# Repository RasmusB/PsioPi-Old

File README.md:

# PsioPi
Hardware upgrade project for the Psion Series 5/5mx

There is a project log maintained at http://hackaday.io/project/4042 

This repository contains the latest development on the PsioPi project.

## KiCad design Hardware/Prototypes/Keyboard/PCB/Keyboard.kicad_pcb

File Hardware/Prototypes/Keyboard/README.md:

# Keyboard prototype

An ATmega32u4 based keyboard controller.

* PCB contains KiCad files for a prototype USB board
* Psion-Keyboard-Firmware contains an Arduino sketch for the firmware
* ScanTheMatrix is a sketch for scanning the matrix of an unknown keyboard

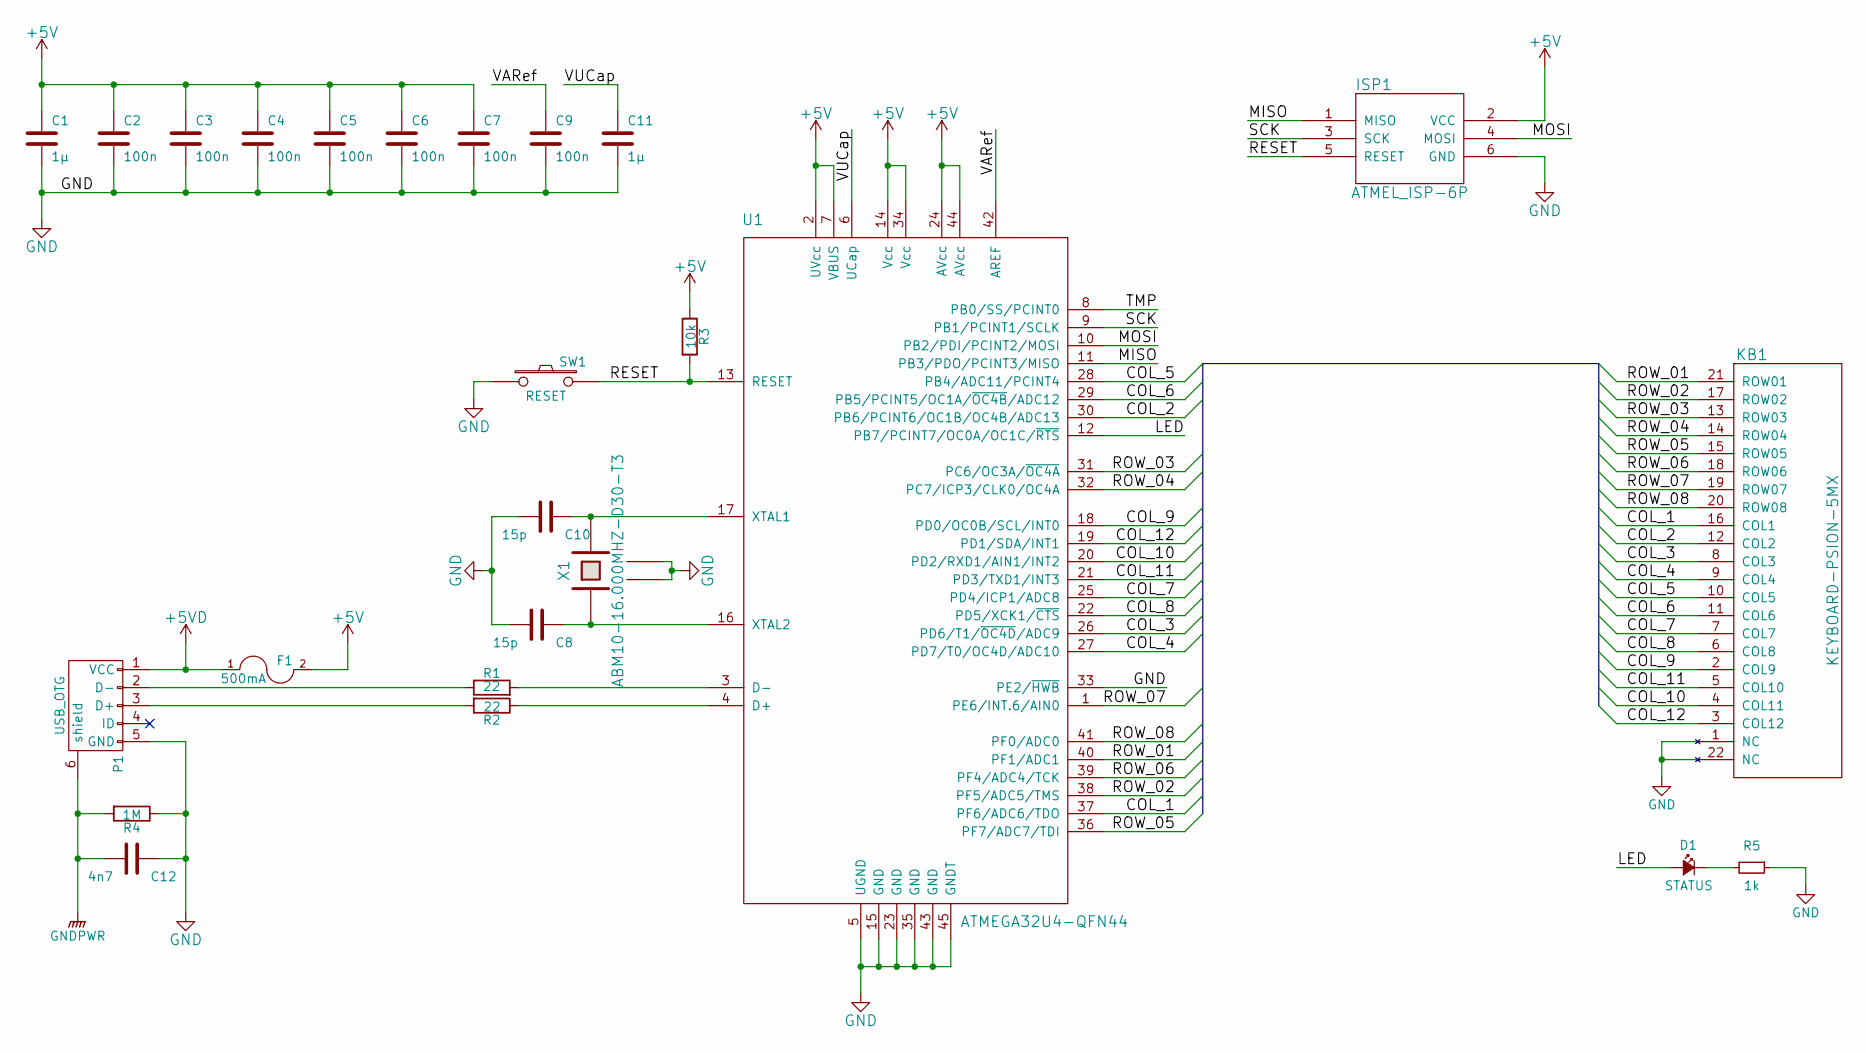
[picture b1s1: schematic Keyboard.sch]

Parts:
C1, C11: 1µ; C-0402-1005
C2, C3, C4, C5, C6, C7, C9: 100n; C-0402-1005
C8, C10: 15p; C-0402-1005
C12: 4n7; C-0402-1005
D1: STATUS; LED-0402-1005
F1: 500mA; F-0603-1608; Farnell 1717227
ISP1: ATMEL_ISP-6P; ISP-PADS_2mm54
KB1: KEYBOARD-PSION-5MX; FPC_0.5mm_22p-MOLEX_52437; Farnell 2520146
P1: USB_OTG; USB-MICRO-MOLEX-47491-0001; Farnell 1568025
R1, R2: 22; R-0402-1005
R3: 10k; R-0402-1005
R4: 1M; R-0402-1005
R5: 1k; R-0402-1005
SW1: RESET; KSR251GLFS; Farnell 2376538
U1: ATMEGA32U4-QFN44; VQFN-44_ATMEL; Farnell 2425127
X1: ABM10-16.000MHZ-D30-T3; 2.5x2mm; Farnell 2467762

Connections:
+5V: C1.1, C2.1, C3.1, C4.1, C5.1, C6.1, C7.1, F1.2, ISP1.2 (VCC), R3.1, U1.2 (UVcc), U1.7 (VBUS), U1.14 (Vcc), U1.24 (AVcc), U1.34 (Vcc), U1.44 (AVcc)
+5VD: F1.1, P1.1 (VCC)
/COL_1: KB1.16 (COL1), U1.37 (PF6/ADC6/TDO)
/COL_2: KB1.12 (COL2), U1.30 (PB6/PCINT6/OC1B/OC4B/ADC13)
/COL_3: KB1.8 (COL3), U1.26 (PD6/T1/~OC4D~/ADC9)
/COL_4: KB1.9 (COL4), U1.27 (PD7/T0/OC4D/ADC10)
/COL_5: KB1.10 (COL5), U1.28 (PB4/ADC11/PCINT4)
/COL_6: KB1.11 (COL6), U1.29 (PB5/PCINT5/OC1A/~OC4B~/ADC12)
/COL_7: KB1.7 (COL7), U1.25 (PD4/ICP1/ADC8)
/COL_8: KB1.6 (COL8), U1.22 (PD5/XCK1/~CTS)
/COL_9: KB1.2 (COL9), U1.18 (PD0/OC0B/SCL/INT0)
/COL_10: KB1.4 (COL11), U1.20 (PD2/RXD1/AIN1/INT2)
/COL_11: KB1.5 (COL10), U1.21 (PD3/TXD1/INT3)
/COL_12: KB1.3 (COL12), U1.19 (PD1/SDA/INT1)
/LED: D1.2 (A), U1.12 (PB7/PCINT7/OC0A/OC1C/~RTS)
/MISO: ISP1.1 (MISO), U1.11 (PB3/PDO/PCINT3/MISO)
/MOSI: ISP1.4 (MOSI), U1.10 (PB2/PDI/PCINT2/MOSI)
/RESET: ISP1.5 (RESET), R3.2, SW1.2, U1.13 (RESET)
/ROW_01: KB1.21 (ROW01), U1.40 (PF1/ADC1)
/ROW_02: KB1.17 (ROW02), U1.38 (PF5/ADC5/TMS)
/ROW_03: KB1.13 (ROW03), U1.31 (PC6/OC3A/~OC4A)
/ROW_04: KB1.14 (ROW04), U1.32 (PC7/ICP3/CLK0/OC4A)
/ROW_05: KB1.15 (ROW05), U1.36 (PF7/ADC7/TDI)
/ROW_06: KB1.18 (ROW06), U1.39 (PF4/ADC4/TCK)
/ROW_07: KB1.19 (ROW07), U1.1 (PE6/INT.6/AIN0)
/ROW_08: KB1.20 (ROW08), U1.41 (PF0/ADC0)
/SCK: ISP1.3 (SCK), U1.9 (PB1/PCINT1/SCLK)
/VARef: C9.1, U1.42 (AREF)
/VUCap: C11.1, U1.6 (UCap)
GND: C1.2, C2.2, C3.2, C4.2, C5.2, C6.2, C7.2, C8.2, C9.2, C10.2, C11.2, C12.1, ISP1.6 (GND), KB1.1 (NC), KB1.22 (NC), P1.5 (GND), R4.1, R5.1, SW1.1, U1.5 (UGND), U1.15 (GND), U1.23 (GND), U1.33 (PE2/~HWB), U1.35 (GND), U1.43 (GND), U1.45 (GNDT), X1.2 (GND), X1.4 (GND)
GNDPWR: C12.2, P1.6 (shield), R4.2
unnamed: C8.1, U1.16 (XTAL2), X1.1
unnamed: C10.1, U1.17 (XTAL1), X1.3
unnamed: D1.1 (K), R5.2
unnamed: P1.2 (D-), R1.1
unnamed: P1.3 (D+), R2.2
unnamed: R1.2, U1.3 (D-)
unnamed: R2.1, U1.4 (D+)

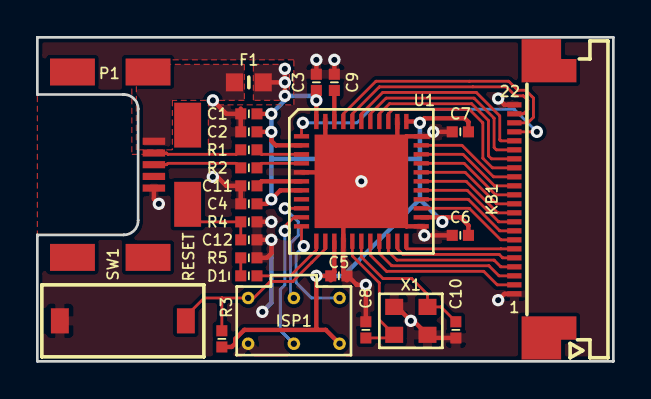
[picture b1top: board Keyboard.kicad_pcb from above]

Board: 2 copper layers, 32.0 x 18.0 mm, 25 parts (0 on the bottom side), 38 nets.

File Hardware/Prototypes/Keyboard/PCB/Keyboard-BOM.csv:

Reference, Value, Footprint, Datasheet, Farnell
KB1,KEYBOARD-PSION-5MX,SMD-Connectors:FPC_0.5mm_22p-MOLEX_52437,,2520146
U1,ATMEGA32U4-QFN44,SMD-QFN:VQFN-44_ATMEL,,2425127
C4,100n,SMD-DiscreteB:C-0402-1005,
C5,100n,SMD-DiscreteB:C-0402-1005,
C6,100n,SMD-DiscreteB:C-0402-1005,
C7,100n,SMD-DiscreteB:C-0402-1005,
C1,1µ,SMD-DiscreteB:C-0402-1005,
C3,100n,SMD-DiscreteB:C-0402-1005,
C9,100n,SMD-DiscreteB:C-0402-1005,
C11,1µ,SMD-DiscreteB:C-0402-1005,
X1,ABM10-16.000MHZ-D30-T3,SMD-XTAL:2.5x2mm,,2467762
C10,15p,SMD-DiscreteB:C-0402-1005,
C8,15p,SMD-DiscreteB:C-0402-1005,
C2,100n,SMD-DiscreteB:C-0402-1005,
R1,22,SMD-DiscreteB:R-0402-1005,
R2,22,SMD-DiscreteB:R-0402-1005,
F1,500mA,SMD-DiscreteB:0603-1608,,1717227
R3,10k,SMD-DiscreteB:R-0402-1005,
ISP1,ATMEL_ISP-6P,SMD-Connectors:ISP-PADS_2mm54,
P1,USB_OTG,SMD-Connectors:USB-MICRO-MOLEX-47491-0001,,1568025
R4,1M,SMD-DiscreteB:R-0402-1005,
C12,4n7,SMD-DiscreteB:C-0402-1005,
D1,STATUS,SMD-DiscreteB:LED-0402-1005,
R5,1k,SMD-DiscreteB:R-0402-1005,
SW1,RESET,SMD-Switches:KSR251GLFS,,2376538

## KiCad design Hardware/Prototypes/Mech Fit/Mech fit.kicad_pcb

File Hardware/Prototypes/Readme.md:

# Prototypes

This folder contains prototypes of different sub-modules. None of these are needed for building a PsioPi, but if you want to use just part of the project, these modules might be a good place to start.

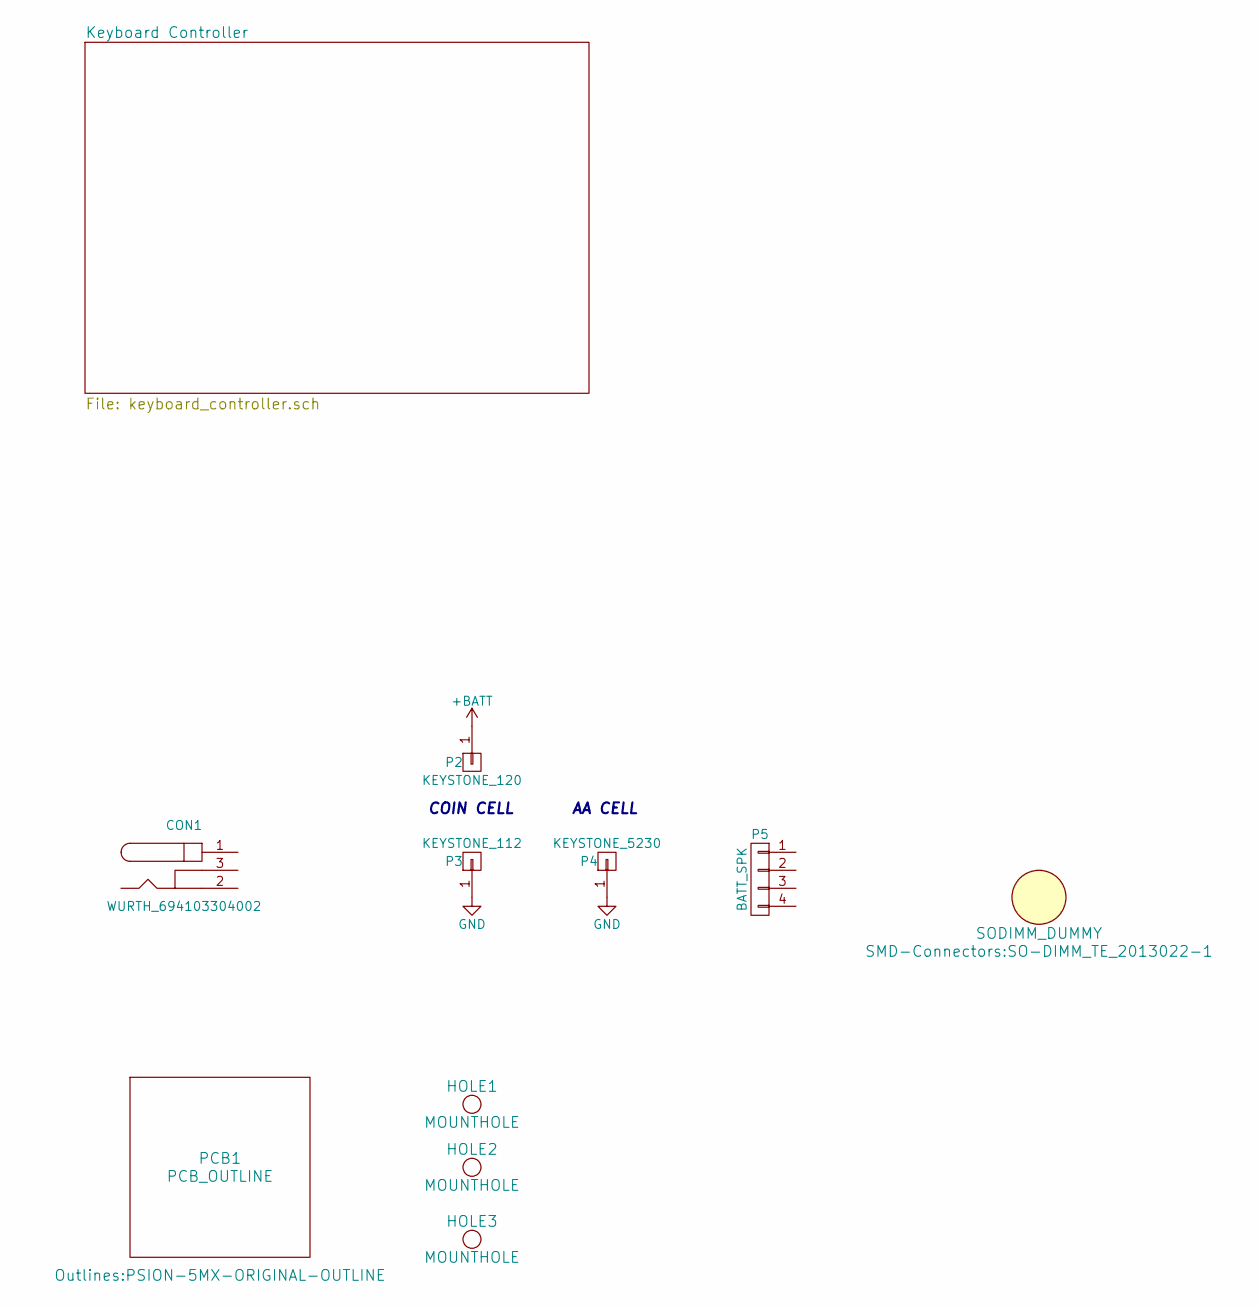
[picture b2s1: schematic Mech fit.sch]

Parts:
CON1: WURTH_694103304002; DC-JACK_WURTH-694103304002; Farnell 2472145
HOLE1, HOLE2, HOLE3: MOUNTHOLE; HOLE-2mm2-NPTH
K1: SODIMM_DUMMY; SO-DIMM_TE_2013022-1
P2: KEYSTONE_120; COIN_CELL_POSITIVE-KEYSTONE_120
P3: KEYSTONE_112; COIN_CELL_NEGATIVE-KEYSTONE_112
P4: KEYSTONE_5230; AAA_CELL_CONTACT-KEYSTONE_5230-DUAL
P5: BATT_SPK; FPC_1mm_4p-TE-84953-4; Farnell 1245278
PCB1: PCB_OUTLINE; PSION-5MX-ORIGINAL-OUTLINE

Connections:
GND: P3.1, P4.1; also elsewhere on the board

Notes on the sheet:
COIN CELL
AA CELL

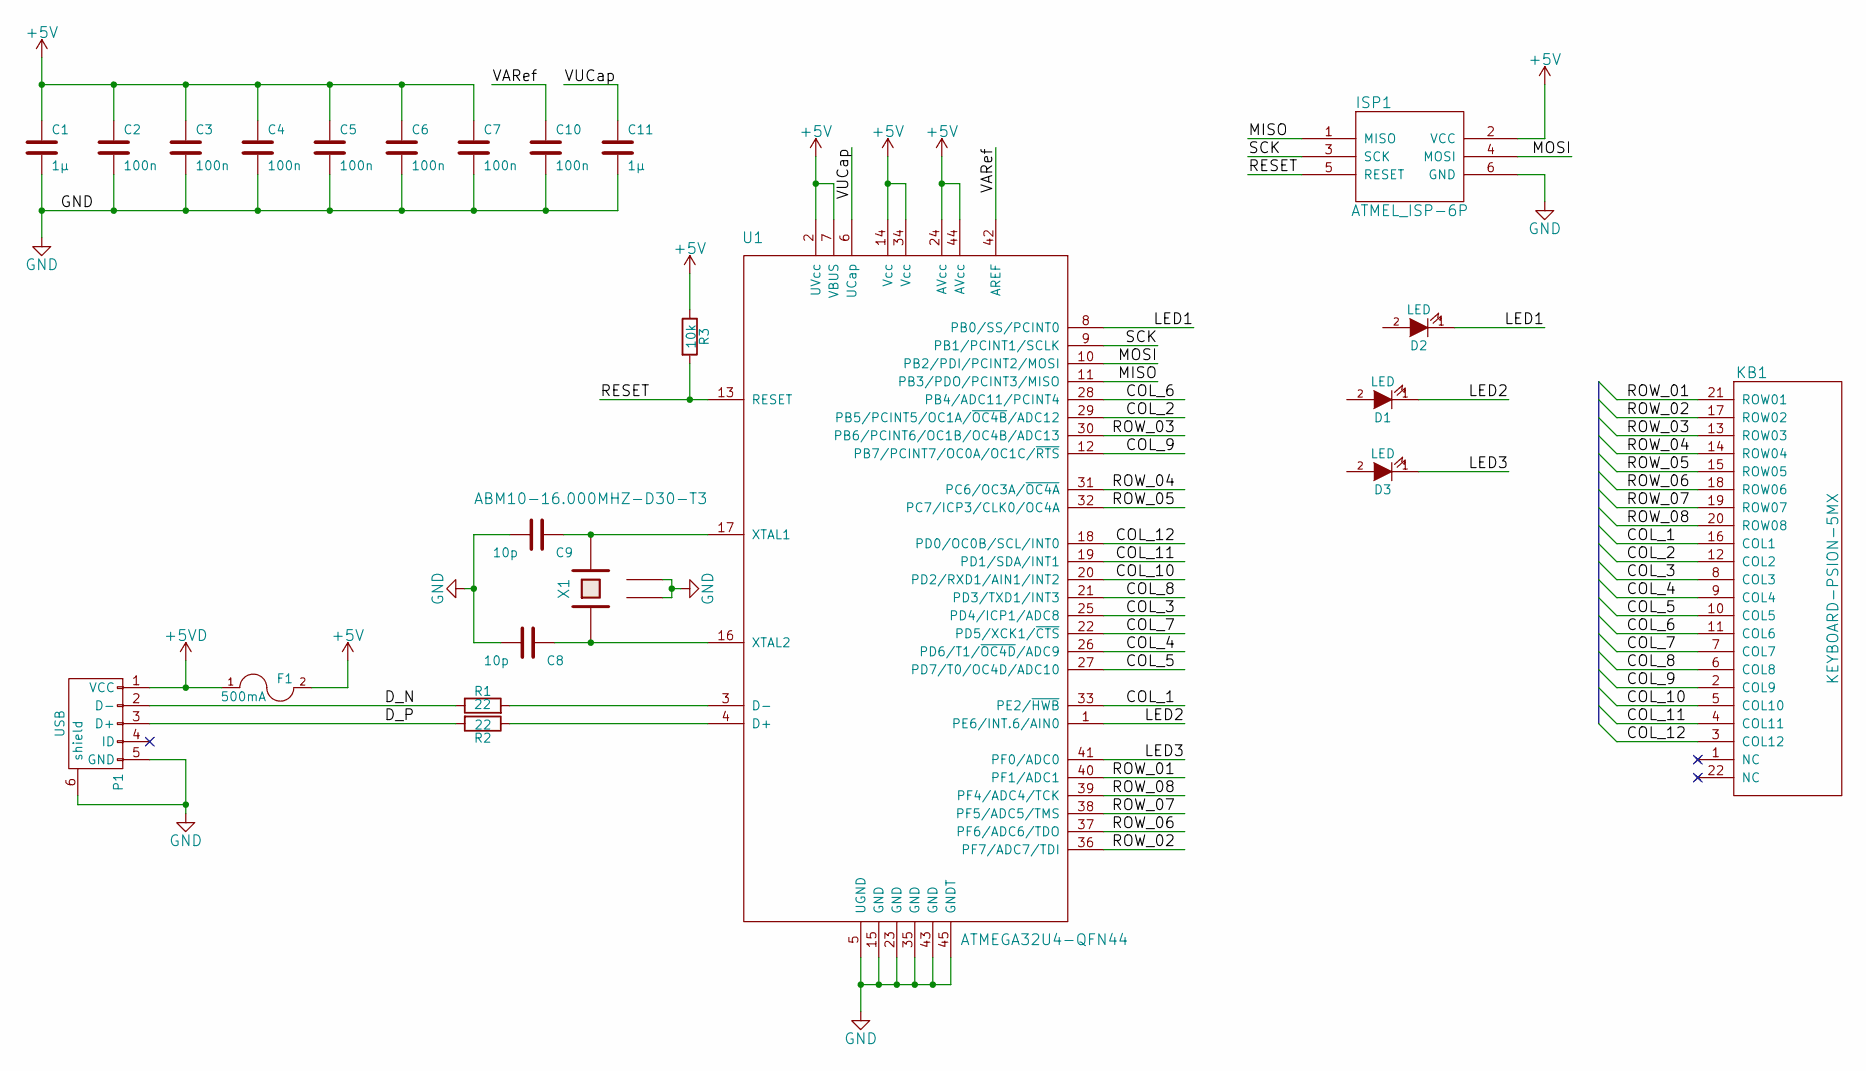
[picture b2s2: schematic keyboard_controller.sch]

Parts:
C1, C11: 1µ; C-0402-1005
C2, C3, C4, C5, C6, C7, C10: 100n; C-0402-1005
C8, C9: 10p; C-0402-1005
D1, D2, D3: LED; LED-0402-1005
F1: 500mA; 0603-1608
ISP1: ATMEL_ISP-6P; ISP-PADS_1x6_2mm54
KB1: KEYBOARD-PSION-5MX; FPC_0mm5_22p-WURTH-68712214522; Farnell 2520146
P1: USB; USB-MICRO-MOLEX-47491-0001; Farnell 1568025
R1, R2: 22; R-0402-1005
R3: 10k; R-0402-1005
U1: ATMEGA32U4-QFN44; VQFN-44_ATMEL
X1: ABM10-16.000MHZ-D30-T3; 2.5x2mm

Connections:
+5V: C1.1, C2.1, C3.1, C4.1, C5.1, C6.1, C7.1, F1.2, ISP1.2 (VCC), R3.1, U1.2 (UVcc), U1.7 (VBUS), U1.14 (Vcc), U1.24 (AVcc), U1.34 (Vcc), U1.44 (AVcc)
+5VD: F1.1, P1.1 (VCC)
/Keyboard Controller/COL_1: KB1.16 (COL1), U1.33 (PE2/~HWB)
/Keyboard Controller/COL_2: KB1.12 (COL2), U1.29 (PB5/PCINT5/OC1A/~OC4B~/ADC12)
/Keyboard Controller/COL_3: KB1.8 (COL3), U1.25 (PD4/ICP1/ADC8)
/Keyboard Controller/COL_4: KB1.9 (COL4), U1.26 (PD6/T1/~OC4D~/ADC9)
/Keyboard Controller/COL_5: KB1.10 (COL5), U1.27 (PD7/T0/OC4D/ADC10)
/Keyboard Controller/COL_6: KB1.11 (COL6), U1.28 (PB4/ADC11/PCINT4)
/Keyboard Controller/COL_7: KB1.7 (COL7), U1.22 (PD5/XCK1/~CTS)
/Keyboard Controller/COL_8: KB1.6 (COL8), U1.21 (PD3/TXD1/INT3)
/Keyboard Controller/COL_9: KB1.2 (COL9), U1.12 (PB7/PCINT7/OC0A/OC1C/~RTS)
/Keyboard Controller/COL_10: KB1.5 (COL10), U1.20 (PD2/RXD1/AIN1/INT2)
/Keyboard Controller/COL_11: KB1.4 (COL11), U1.19 (PD1/SDA/INT1)
/Keyboard Controller/COL_12: KB1.3 (COL12), U1.18 (PD0/OC0B/SCL/INT0)
/Keyboard Controller/D_N: P1.2 (D-), R1.1
/Keyboard Controller/D_P: P1.3 (D+), R2.2
/Keyboard Controller/LED1: D2.1 (K), U1.8 (PB0/SS/PCINT0)
/Keyboard Controller/LED2: D1.1 (K), U1.1 (PE6/INT.6/AIN0)
/Keyboard Controller/LED3: D3.1 (K), U1.41 (PF0/ADC0)
/Keyboard Controller/MISO: ISP1.1 (MISO), U1.11 (PB3/PDO/PCINT3/MISO)
/Keyboard Controller/MOSI: ISP1.4 (MOSI), U1.10 (PB2/PDI/PCINT2/MOSI)
/Keyboard Controller/RESET: ISP1.5 (RESET), R3.2, U1.13 (RESET)
/Keyboard Controller/ROW_01: KB1.21 (ROW01), U1.40 (PF1/ADC1)
/Keyboard Controller/ROW_02: KB1.17 (ROW02), U1.36 (PF7/ADC7/TDI)
/Keyboard Controller/ROW_03: KB1.13 (ROW03), U1.30 (PB6/PCINT6/OC1B/OC4B/ADC13)
/Keyboard Controller/ROW_04: KB1.14 (ROW04), U1.31 (PC6/OC3A/~OC4A)
/Keyboard Controller/ROW_05: KB1.15 (ROW05), U1.32 (PC7/ICP3/CLK0/OC4A)
/Keyboard Controller/ROW_06: KB1.18 (ROW06), U1.37 (PF6/ADC6/TDO)
/Keyboard Controller/ROW_07: KB1.19 (ROW07), U1.38 (PF5/ADC5/TMS)
/Keyboard Controller/ROW_08: KB1.20 (ROW08), U1.39 (PF4/ADC4/TCK)
/Keyboard Controller/SCK: ISP1.3 (SCK), U1.9 (PB1/PCINT1/SCLK)
/Keyboard Controller/VARef: C10.1, U1.42 (AREF)
/Keyboard Controller/VUCap: C11.1, U1.6 (UCap)
GND: C1.2, C2.2, C3.2, C4.2, C5.2, C6.2, C7.2, C8.2, C9.2, C10.2, C11.2, ISP1.6 (GND), P1.5 (GND), P1.6 (shield), U1.5 (UGND), U1.15 (GND), U1.23 (GND), U1.35 (GND), U1.43 (GND), U1.45 (GNDT), X1.2 (GND), X1.4 (GND); also elsewhere on the board
unnamed: C8.1, U1.16 (XTAL2), X1.1
unnamed: C9.1, U1.17 (XTAL1), X1.3
unnamed: R1.2, U1.3 (D-)
unnamed: R2.1, U1.4 (D+)

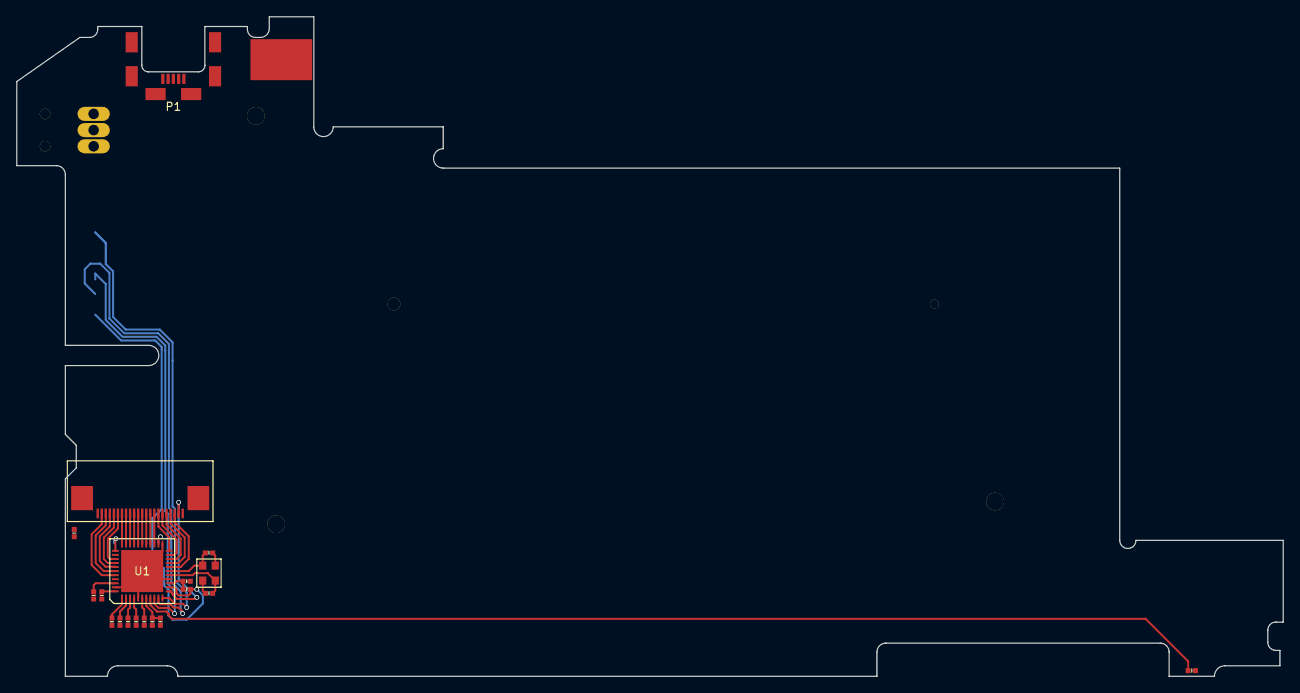
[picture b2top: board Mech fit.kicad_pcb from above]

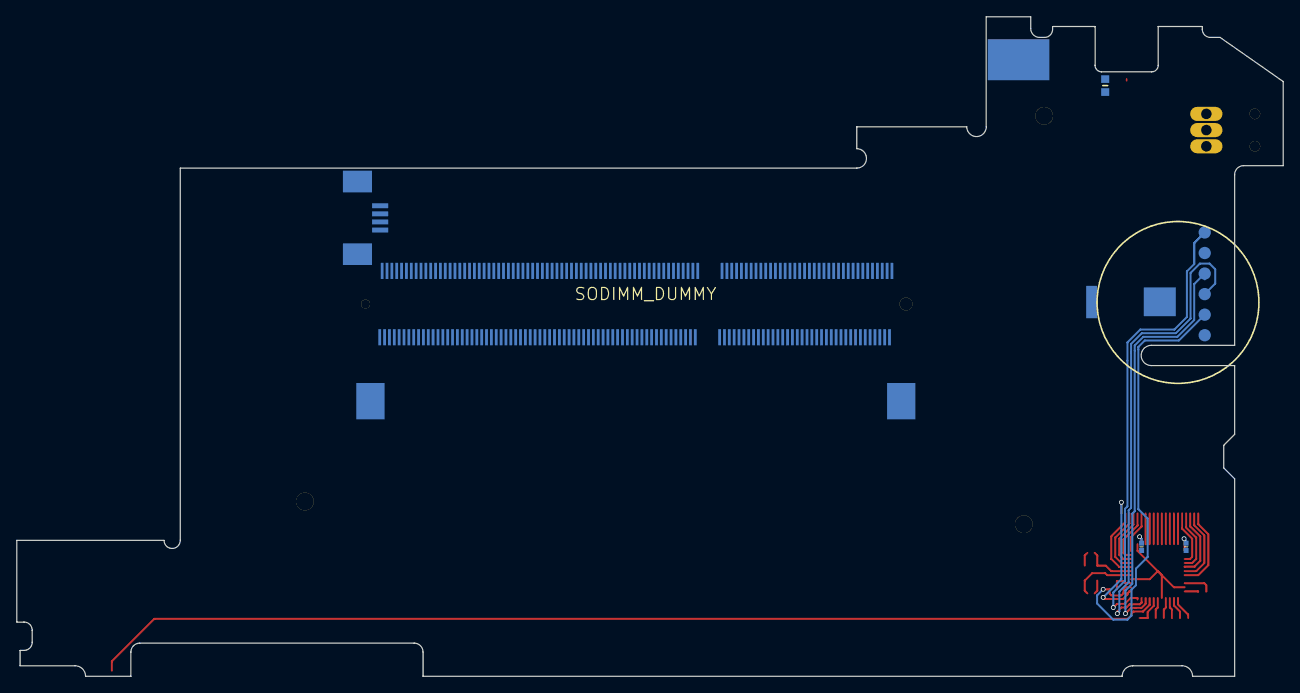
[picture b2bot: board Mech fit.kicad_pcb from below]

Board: 2 copper layers, 156.5 x 81.5 mm, 33 parts (9 on the bottom side), 38 nets.

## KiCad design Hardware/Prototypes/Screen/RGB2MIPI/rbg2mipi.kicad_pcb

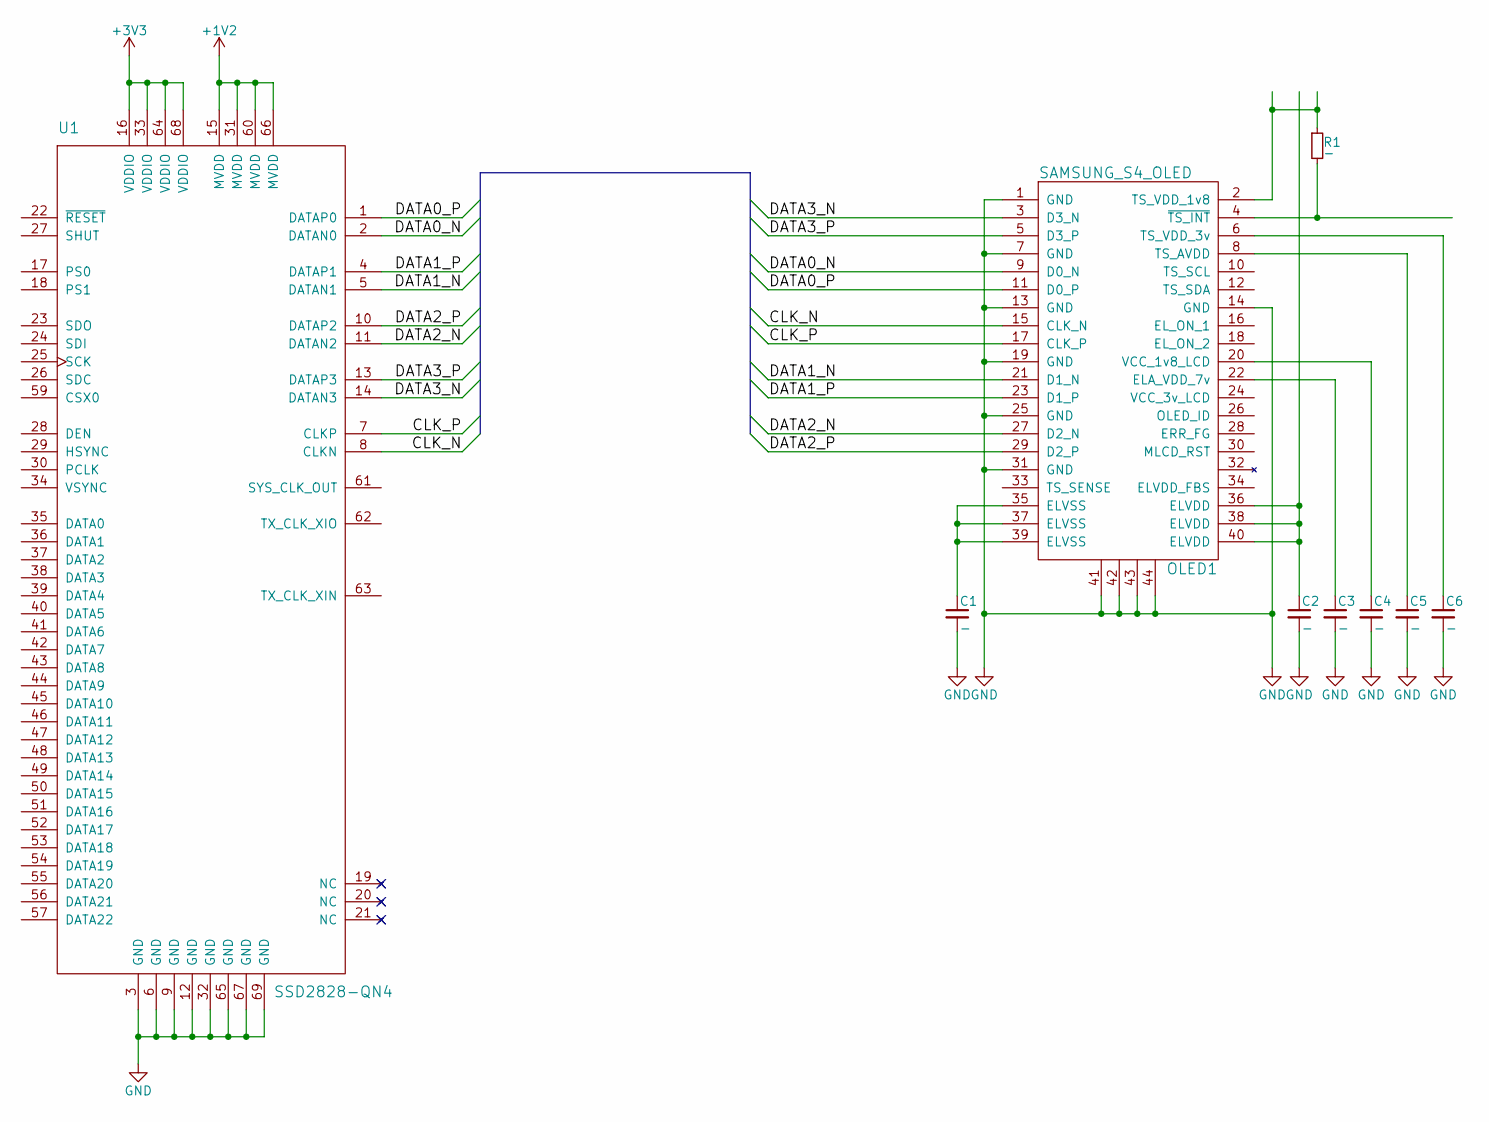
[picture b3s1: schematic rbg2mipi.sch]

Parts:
C1, C2, C3, C4, C5, C6: -; C-0402-1005
OLED1: SAMSUNG_S4_OLED; PANASONIC-AXE640124-SAMSUNG-S4
R1: -; R-0402-1005
U1: SSD2828-QN4; QFN64_8x8mm_0mm4-SSD

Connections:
+1V2: U1.15 (MVDD), U1.31 (MVDD), U1.60 (MVDD), U1.66 (MVDD)
+3V3: U1.16 (VDDIO), U1.33 (VDDIO), U1.64 (VDDIO), U1.68 (VDDIO)
/CLK_N: OLED1.15 (CLK_N), U1.8 (CLKN)
/CLK_P: OLED1.17 (CLK_P), U1.7 (CLKP)
/DATA0_N: OLED1.9 (D0_N), U1.2 (DATAN0)
/DATA0_P: OLED1.11 (D0_P), U1.1 (DATAP0)
/DATA1_N: OLED1.21 (D1_N), U1.5 (DATAN1)
/DATA1_P: OLED1.23 (D1_P), U1.4 (DATAP1)
/DATA2_N: OLED1.27 (D2_N), U1.11 (DATAN2)
/DATA2_P: OLED1.29 (D2_P), U1.10 (DATAP2)
/DATA3_N: OLED1.3 (D3_N), U1.14 (DATAN3)
/DATA3_P: OLED1.5 (D3_P), U1.13 (DATAP3)
GND: C1.2, C2.2, C3.2, C4.2, C5.2, C6.2, OLED1.1 (GND), OLED1.7 (GND), OLED1.13 (GND), OLED1.14 (GND), OLED1.19 (GND), OLED1.25 (GND), OLED1.31 (GND), OLED1.41, OLED1.42, OLED1.43, OLED1.44, U1.3 (GND), U1.6 (GND), U1.9 (GND), U1.12 (GND), U1.32 (GND), U1.65 (GND), U1.67 (GND), U1.69 (GND)
unnamed: C1.1, OLED1.35 (ELVSS), OLED1.37 (ELVSS), OLED1.39 (ELVSS)
unnamed: C2.1, OLED1.36 (ELVDD), OLED1.38 (ELVDD), OLED1.40 (ELVDD)
unnamed: C3.1, OLED1.22 (ELA_VDD_7v)
unnamed: C4.1, OLED1.20 (VCC_1v8_LCD)
unnamed: C5.1, OLED1.8 (TS_AVDD)
unnamed: C6.1, OLED1.6 (TS_VDD_3v)
unnamed: OLED1.2 (TS_VDD_1v8), R1.1
unnamed: OLED1.4 (~TS_INT), R1.2

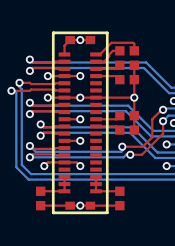
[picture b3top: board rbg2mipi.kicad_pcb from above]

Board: 2 copper layers, 9 parts (1 on the bottom side), 21 nets.

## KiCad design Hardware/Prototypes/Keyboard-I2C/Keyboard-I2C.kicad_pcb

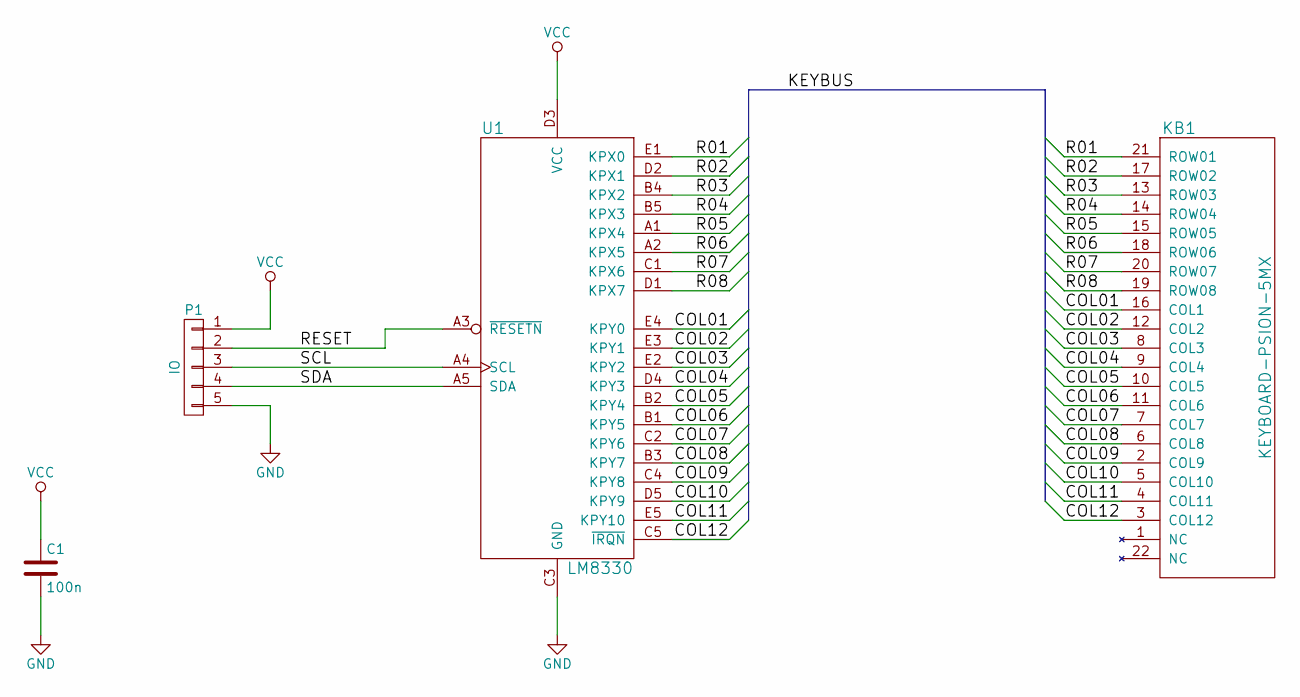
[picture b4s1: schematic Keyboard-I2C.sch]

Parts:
C1: 100n; C-0402-1005
KB1: KEYBOARD-PSION-5MX; FPC_0.5mm_22p-MOLEX_52437
P1: IO; PIN_HEADER-1x5
U1: LM8330; DSBGA-25_2x2_0mm4

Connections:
/COL01: KB1.16 (COL1), U1.E4 (KPY0)
/COL02: KB1.12 (COL2), U1.E3 (KPY1)
/COL03: KB1.8 (COL3), U1.E2 (KPY2)
/COL04: KB1.9 (COL4), U1.D4 (KPY3)
/COL05: KB1.10 (COL5), U1.B2 (KPY4)
/COL06: KB1.11 (COL6), U1.B1 (KPY5)
/COL07: KB1.7 (COL7), U1.C2 (KPY6)
/COL08: KB1.6 (COL8), U1.B3 (KPY7)
/COL09: KB1.2 (COL9), U1.C4 (KPY8)
/COL10: KB1.5 (COL10), U1.D5 (KPY9)
/COL11: KB1.4 (COL11), U1.E5 (KPY10)
/COL12: KB1.3 (COL12), U1.C5 (~IRQN)
/R01: KB1.21 (ROW01), U1.E1 (KPX0)
/R02: KB1.17 (ROW02), U1.D2 (KPX1)
/R03: KB1.13 (ROW03), U1.B4 (KPX2)
/R04: KB1.14 (ROW04), U1.B5 (KPX3)
/R05: KB1.15 (ROW05), U1.A1 (KPX4)
/R06: KB1.18 (ROW06), U1.A2 (KPX5)
/R07: KB1.20 (ROW07), U1.C1 (KPX6)
/R08: KB1.19 (ROW08), U1.D1 (KPX7)
/RESET: P1.2, U1.A3 (~RESETN)
/SCL: P1.3, U1.A4 (SCL)
/SDA: P1.4, U1.A5 (SDA)
GND: C1.2, P1.5, U1.C3 (GND)
VCC: C1.1, P1.1, U1.D3 (VCC)

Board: 2 copper layers, 4 parts (0 on the bottom side), 25 nets, no tracks yet.

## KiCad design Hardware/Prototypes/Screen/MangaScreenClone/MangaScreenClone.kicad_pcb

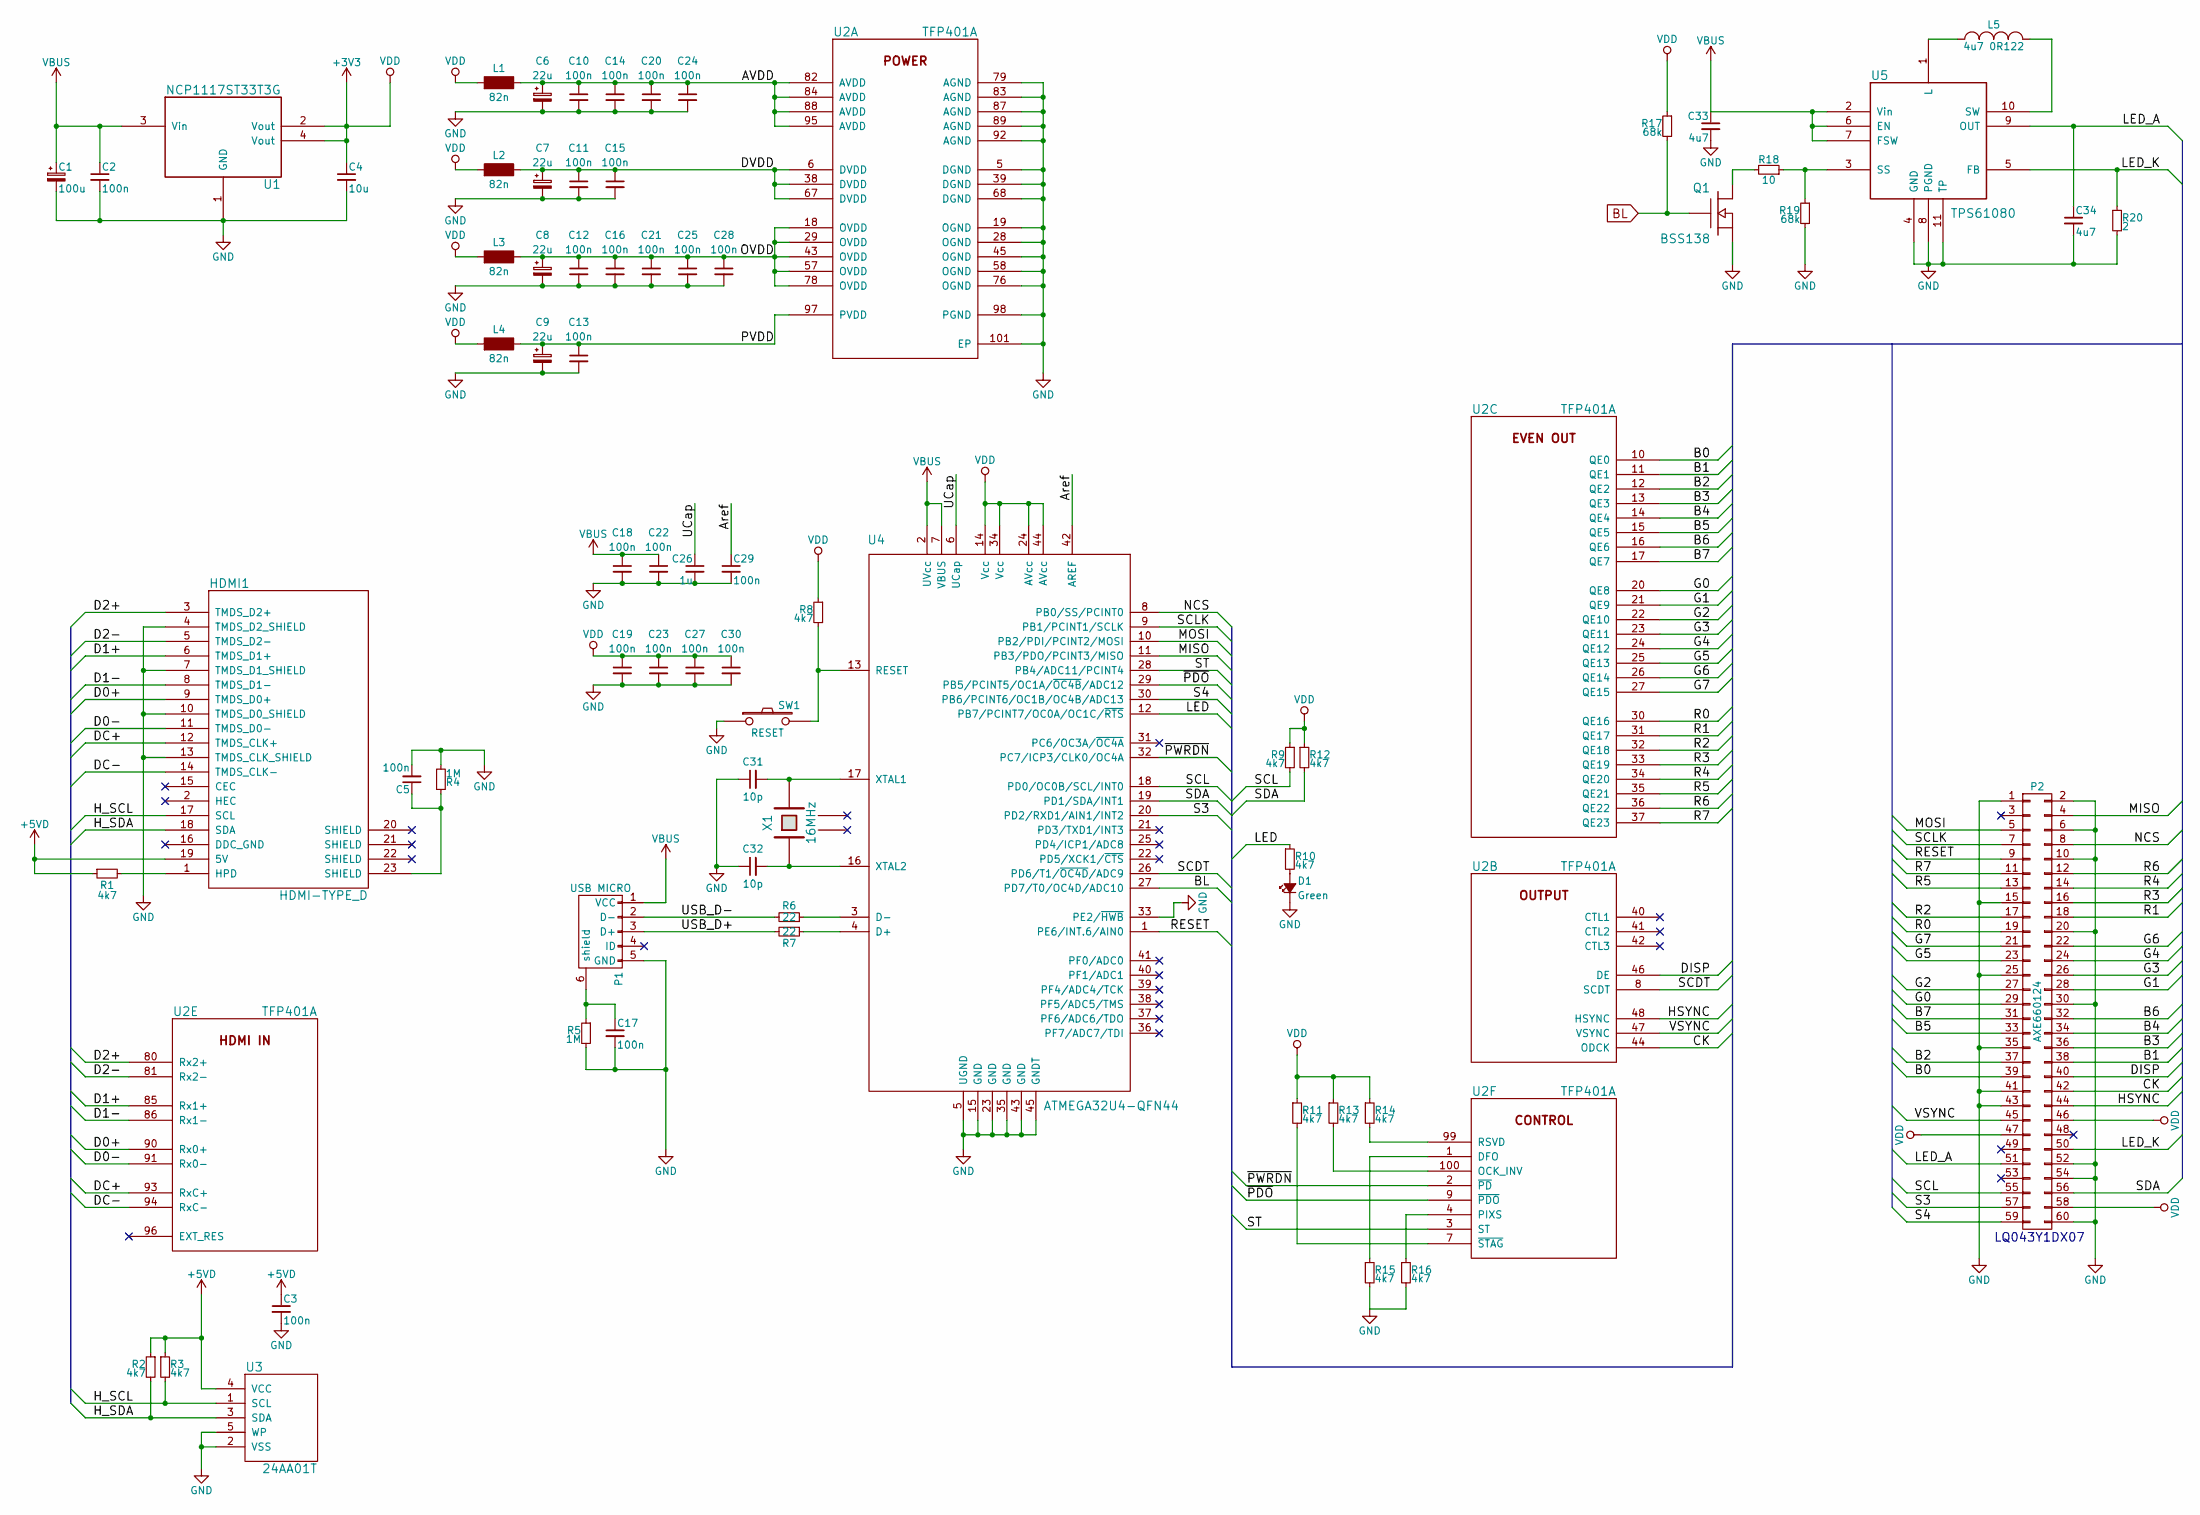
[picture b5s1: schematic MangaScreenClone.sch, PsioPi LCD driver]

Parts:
C1: 100u; B-3528-21; Farnell 1658510
C2, C3, C5, C10, C11, C12, C13, C14, C15, C16, C17, C18, C19, C20, C21, C22, C23, C24, C25, C27, C28, C29, C30: 100n; C-0402-1005
C4: 10u; C-0402-1005; Farnell 2218854
C6, C7, C8, C9: 22u; A-3216-18; Farnell 1457420
C26: 1u; C-0402-1005
C31, C32: 10p; C-0402-1005
C33, C34: 4u7; C-0402-1005
D1: Green; LED-0402-1005
HDMI1: HDMI-TYPE_D; HDMI-D_MOLEX_46765-0301
L1, L2, L3, L4: 82n; 0805-2012; Farnell 1669556
L5: 4u7 0R122; L_5x5mm_TDK-VLCF5020--1; Farnell 1670111
P1: USB MICRO; USB-MICRO-10104110-0001LF
P2: AXE660124; DigiKey 255-3214-1-ND
Q1: BSS138; SOT-23
R1, R2, R3, R8, R9, R10, R11, R12, R13, R14, R15, R16: 4k7; R-0402-1005
R4, R5: 1M; R-0402-1005
R6, R7: 22; R-0402-1005
R17, R19: 68k; R-0402-1005
R18: 10; R-0402-1005
R20: 2; 0603-1608
SW1: RESET; ALPS-SKQGAFE010
U1: NCP1117ST33T3G; SOT-223; Farnell 1652366
U2: TFP401A; PQFP-100_0mm5
U3: 24AA01T; SOT-23-5_TI-DBV; Farnell 1331269
U4: ATMEGA32U4-QFN44; VQFN-44_ATMEL
U5: TPS61080; PVSON-N10; Farnell 1344378
X1: 16MHz; 2.5x2mm

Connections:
+3V3: C4.1, C19.1, C23.1, C27.1, C30.1, L1.2, L2.2, L3.2, L4.2, P2.46, P2.47, P2.58, R8.1, R9.1, R11.1, R12.1, R13.1, R14.1, R17.1, U1.2 (Vout), U1.4 (Vout), U4.14 (Vcc), U4.24 (AVcc), U4.34 (Vcc), U4.44 (AVcc)
+5VD: C3.1, HDMI1.19 (5V), R1.1, R2.1, R3.1, U3.4 (VCC)
/AVDD: C6.1, C10.1, C14.1, C20.1, C24.1, L1.1, U2.82 (AVDD), U2.84 (AVDD), U2.88 (AVDD), U2.95 (AVDD)
/Aref: C29.1, U4.42 (AREF)
/B0: P2.39, U2.10 (QE0)
/B1: P2.38, U2.11 (QE1)
/B2: P2.37, U2.12 (QE2)
/B3: P2.36, U2.13 (QE3)
/B4: P2.34, U2.14 (QE4)
/B5: P2.33, U2.15 (QE5)
/B6: P2.32, U2.16 (QE6)
/B7: P2.31, U2.17 (QE7)
/CK: P2.42, U2.44 (ODCK)
/D0+: HDMI1.9 (TMDS_D0+), U2.90 (Rx0+)
/D0-: HDMI1.11 (TMDS_D0-), U2.91 (Rx0-)
/D1+: HDMI1.6 (TMDS_D1+), U2.85 (Rx1+)
/D1-: HDMI1.8 (TMDS_D1-), U2.86 (Rx1-)
/D2+: HDMI1.3 (TMDS_D2+), U2.80 (Rx2+)
/D2-: HDMI1.5 (TMDS_D2-), U2.81 (Rx2-)
/DC+: HDMI1.12 (TMDS_CLK+), U2.93 (RxC+)
/DC-: HDMI1.14 (TMDS_CLK-), U2.94 (RxC-)
/DISP: P2.40, U2.46 (DE)
/DVDD: C7.1, C11.1, C15.1, L2.1, U2.6 (DVDD), U2.38 (DVDD), U2.67 (DVDD)
/G0: P2.29, U2.20 (QE8)
/G1: P2.28, U2.21 (QE9)
/G2: P2.27, U2.22 (QE10)
/G3: P2.26, U2.23 (QE11)
/G4: P2.24, U2.24 (QE12)
/G5: P2.23, U2.25 (QE13)
/G6: P2.22, U2.26 (QE14)
/G7: P2.21, U2.27 (QE15)
/HSYNC: P2.44, U2.48 (HSYNC)
/H_SCL: HDMI1.17 (SCL), R3.2, U3.1 (SCL)
/H_SDA: HDMI1.18 (SDA), R2.2, U3.3 (SDA)
/LED: R10.1, U4.12 (PB7/PCINT7/OC0A/OC1C/~RTS)
/LED_A: C34.1, P2.51, U5.9 (OUT)
/LED_K: P2.50, R20.1, U5.5 (FB)
/MISO: P2.4, U4.11 (PB3/PDO/PCINT3/MISO)
/MOSI: P2.5, U4.10 (PB2/PDI/PCINT2/MOSI)
/NCS: P2.8, U4.8 (PB0/SS/PCINT0)
/OVDD: C8.1, C12.1, C16.1, C21.1, C25.1, C28.1, L3.1, U2.18 (OVDD), U2.29 (OVDD), U2.43 (OVDD), U2.57 (OVDD), U2.78 (OVDD)
/PVDD: C9.1, C13.1, L4.1, U2.97 (PVDD)
/R0: P2.19, U2.30 (QE16)
/R1: P2.18, U2.31 (QE17)
/R2: P2.17, U2.32 (QE18)
/R3: P2.16, U2.33 (QE19)
/R4: P2.14, U2.34 (QE20)
/R5: P2.13, U2.35 (QE21)
/R6: P2.12, U2.36 (QE22)
/R7: P2.11, U2.37 (QE23)
/RESET: P2.9, U4.1 (PE6/INT.6/AIN0)
/S3: P2.57, U4.20 (PD2/RXD1/AIN1/INT2)
/S4: P2.59, U4.30 (PB6/PCINT6/OC1B/OC4B/ADC13)
/SCDT: U2.8 (SCDT), U4.26 (PD6/T1/~OC4D~/ADC9)
/SCL: P2.55, R9.2, U4.18 (PD0/OC0B/SCL/INT0)
/SCLK: P2.7, U4.9 (PB1/PCINT1/SCLK)
/SDA: P2.56, R12.2, U4.19 (PD1/SDA/INT1)
/ST: U2.3 (ST), U4.28 (PB4/ADC11/PCINT4)
/UCap: C26.1, U4.6 (UCap)
/USB_D+: P1.3 (D+), R7.2
/USB_D-: P1.2 (D-), R6.2
/VSYNC: P2.45, U2.47 (VSYNC)
/~PDO: U2.9 (~PDO), U4.29 (PB5/PCINT5/OC1A/~OC4B~/ADC12)
/~PWRDN: U2.2 (~PD), U4.32 (PC7/ICP3/CLK0/OC4A)
BL: Q1.1, R17.2, U4.27 (PD7/T0/OC4D/ADC10)
GND: C1.2, C2.2, C3.2, C4.2, C5.2, C6.2, C7.2, C8.2, C9.2, C10.2, C11.2, C12.2, C13.2, C14.2, C15.2, C16.2, C17.2, C18.2, C19.2, C20.2, C21.2, C22.2, C23.2, C24.2, C25.2, C26.2, C27.2, C28.2, C29.2, C30.2, C31.1, C32.1, C33.2, C34.2, D1.1 (K), HDMI1.4 (TMDS_D2_SHIELD), HDMI1.7 (TMDS_D1_SHIELD), HDMI1.10 (TMDS_D0_SHIELD), HDMI1.13 (TMDS_CLK_SHIELD), P1.5 (GND), P2.1, P2.2, P2.6, P2.10, P2.15, P2.20, P2.25, P2.30, P2.35, P2.41, P2.43, P2.52, P2.54, P2.60, Q1.2, R4.2, R5.2, R15.2, R16.2, R19.2, R20.2, SW1.1, U1.1 (GND), U2.5 (DGND), U2.19 (OGND), U2.28 (OGND), U2.39 (DGND), U2.45 (OGND), U2.58 (OGND), U2.68 (DGND), U2.76 (OGND), U2.79 (AGND), U2.83 (AGND), U2.87 (AGND), U2.89 (AGND), U2.92 (AGND), U2.98 (PGND), U2.101 (EP), U3.2 (VSS), U3.5 (WP), U4.5 (UGND), U4.15 (GND), U4.23 (GND), U4.33 (PE2/~HWB), U4.35 (GND), U4.43 (GND), U4.45 (GNDT), U5.4 (GND), U5.8 (PGND), U5.11 (TP)
unnamed: C5.1, HDMI1.23 (SHIELD), R4.1
unnamed: C17.1, P1.6 (shield), R5.1
unnamed: C31.2, U4.17 (XTAL1), X1.3
unnamed: C32.2, U4.16 (XTAL2), X1.1
unnamed: D1.2 (A), R10.2
unnamed: HDMI1.1 (HPD), R1.2
unnamed: L5.1, U5.1 (L)
unnamed: L5.2, U5.10 (SW)
unnamed: Q1.3, R18.2
unnamed: R6.1, U4.3 (D-)
unnamed: R7.1, U4.4 (D+)
unnamed: R8.2, SW1.3, U4.13 (RESET)
unnamed: R11.2, U2.7 (~STAG)
unnamed: R13.2, U2.100 (OCK_INV)
unnamed: R14.2, U2.99 (RSVD)
unnamed: R15.1, U2.1 (DFO)
unnamed: R16.1, U2.4 (PIXS)
unnamed: R18.1, R19.1, U5.3 (SS)
VBUS: C1.1, C2.1, C18.1, C22.1, C33.1, P1.1 (VCC), U1.3 (Vin), U4.2 (UVcc), U4.7 (VBUS), U5.2 (Vin), U5.6 (EN), U5.7 (FSW)

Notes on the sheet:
LQ043Y1DX07
